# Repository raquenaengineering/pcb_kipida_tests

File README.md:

# pcb_kipida_tests
PCB to test and validate kipida simulator functionality.

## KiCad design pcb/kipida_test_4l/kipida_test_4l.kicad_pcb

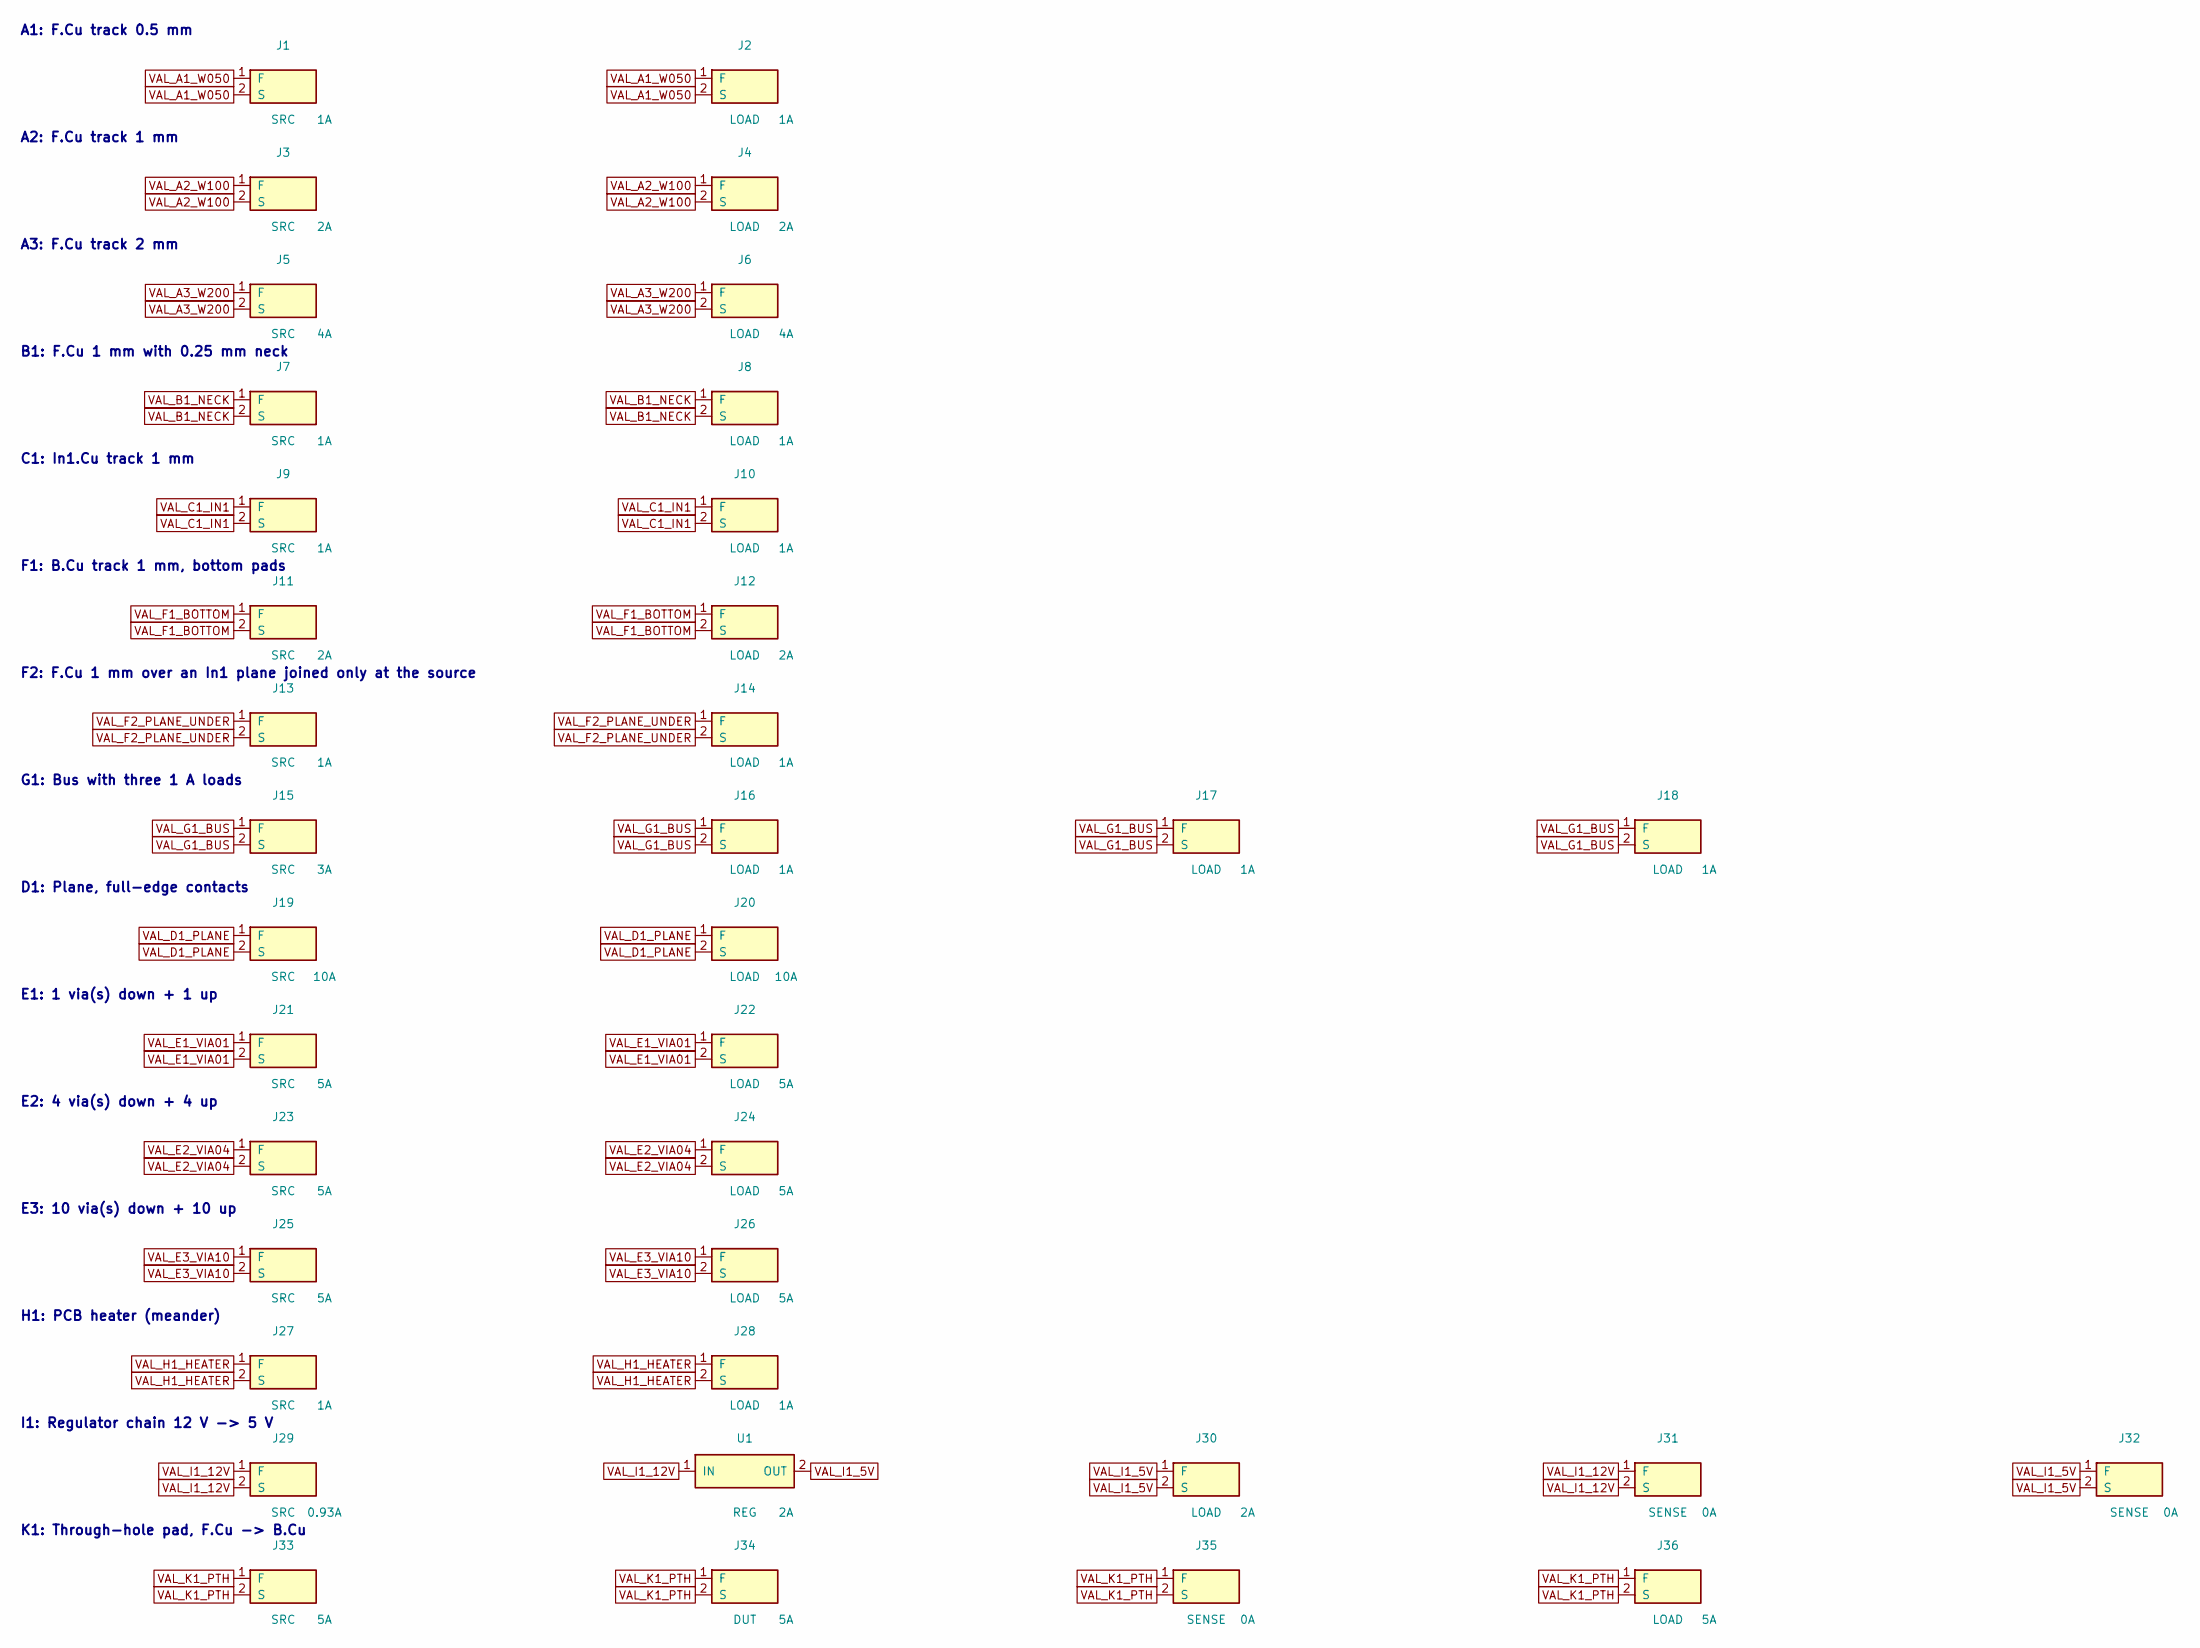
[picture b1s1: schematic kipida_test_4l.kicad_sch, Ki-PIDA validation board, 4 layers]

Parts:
J1: SRC; Terminal_A1_src
J2: LOAD; Terminal_A1_load
J3: SRC; Terminal_A2_src
J4: LOAD; Terminal_A2_load
J5: SRC; Terminal_A3_src
J6: LOAD; Terminal_A3_load
J7: SRC; Terminal_B1_src
J8: LOAD; Terminal_B1_load
J9: SRC; Terminal_C1_src
J10: LOAD; Terminal_C1_load
J11: SRC; Terminal_F1_src
J12: LOAD; Terminal_F1_load
J13: SRC; Terminal_F2_src
J14: LOAD; Terminal_F2_load
J15: SRC; Terminal_G1_src
J16: LOAD; Terminal_G1L1_load
J17: LOAD; Terminal_G1L2_load
J18: LOAD; Terminal_G1L3_load
J19: SRC; Terminal_D1_src
J20: LOAD; Terminal_D1_load
J21: SRC; Terminal_E1_src
J22: LOAD; Terminal_E1_load
J23: SRC; Terminal_E2_src
J24: LOAD; Terminal_E2_load
J25: SRC; Terminal_E3_src
J26: LOAD; Terminal_E3_load
J27: SRC; Terminal_H1_src
J28: LOAD; Terminal_H1_load
J29: SRC; Terminal_I1_src
J30: LOAD; Terminal_I1_load
J31, J32: SENSE; Terminal_I1_sense
J33: SRC; Terminal_K1_src
J34: DUT; Terminal_K1_dut
J35: SENSE; Terminal_K1_sense
J36: LOAD; Terminal_K1_load
U1: REG; Regulator_I1

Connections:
VAL_A1_W050: J1.1 (F), J1.2 (S), J2.1 (F), J2.2 (S)
VAL_A2_W100: J3.1 (F), J3.2 (S), J4.1 (F), J4.2 (S)
VAL_A3_W200: J5.1 (F), J5.2 (S), J6.1 (F), J6.2 (S)
VAL_B1_NECK: J7.1 (F), J7.2 (S), J8.1 (F), J8.2 (S)
VAL_C1_IN1: J9.1 (F), J9.2 (S), J10.1 (F), J10.2 (S)
VAL_D1_PLANE: J19.1 (F), J19.2 (S), J20.1 (F), J20.2 (S)
VAL_E1_VIA01: J21.1 (F), J21.2 (S), J22.1 (F), J22.2 (S)
VAL_E2_VIA04: J23.1 (F), J23.2 (S), J24.1 (F), J24.2 (S)
VAL_E3_VIA10: J25.1 (F), J25.2 (S), J26.1 (F), J26.2 (S)
VAL_F1_BOTTOM: J11.1 (F), J11.2 (S), J12.1 (F), J12.2 (S)
VAL_F2_PLANE_UNDER: J13.1 (F), J13.2 (S), J14.1 (F), J14.2 (S)
VAL_G1_BUS: J15.1 (F), J15.2 (S), J16.1 (F), J16.2 (S), J17.1 (F), J17.2 (S), J18.1 (F), J18.2 (S)
VAL_H1_HEATER: J27.1 (F), J27.2 (S), J28.1 (F), J28.2 (S)
VAL_I1_5V: J30.1 (F), J30.2 (S), J32.1 (F), J32.2 (S), U1.2 (OUT)
VAL_I1_12V: J29.1 (F), J29.2 (S), J31.1 (F), J31.2 (S), U1.1 (IN)
VAL_K1_PTH: J33.1 (F), J33.2 (S), J34.1 (F), J34.2 (S), J35.1 (F), J35.2 (S), J36.1 (F), J36.2 (S)

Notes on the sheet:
A1: F.Cu track 0.5 mm
A2: F.Cu track 1 mm
A3: F.Cu track 2 mm
B1: F.Cu 1 mm with 0.25 mm neck
C1: In1.Cu track 1 mm
F1: B.Cu track 1 mm, bottom pads
F2: F.Cu 1 mm over an In1 plane joined only at the source
G1: Bus with three 1 A loads
D1: Plane, full-edge contacts
E1: 1 via(s) down + 1 up
E2: 4 via(s) down + 4 up
E3: 10 via(s) down + 10 up
H1: PCB heater (meander)
I1: Regulator chain 12 V -> 5 V
K1: Through-hole pad, F.Cu -> B.Cu

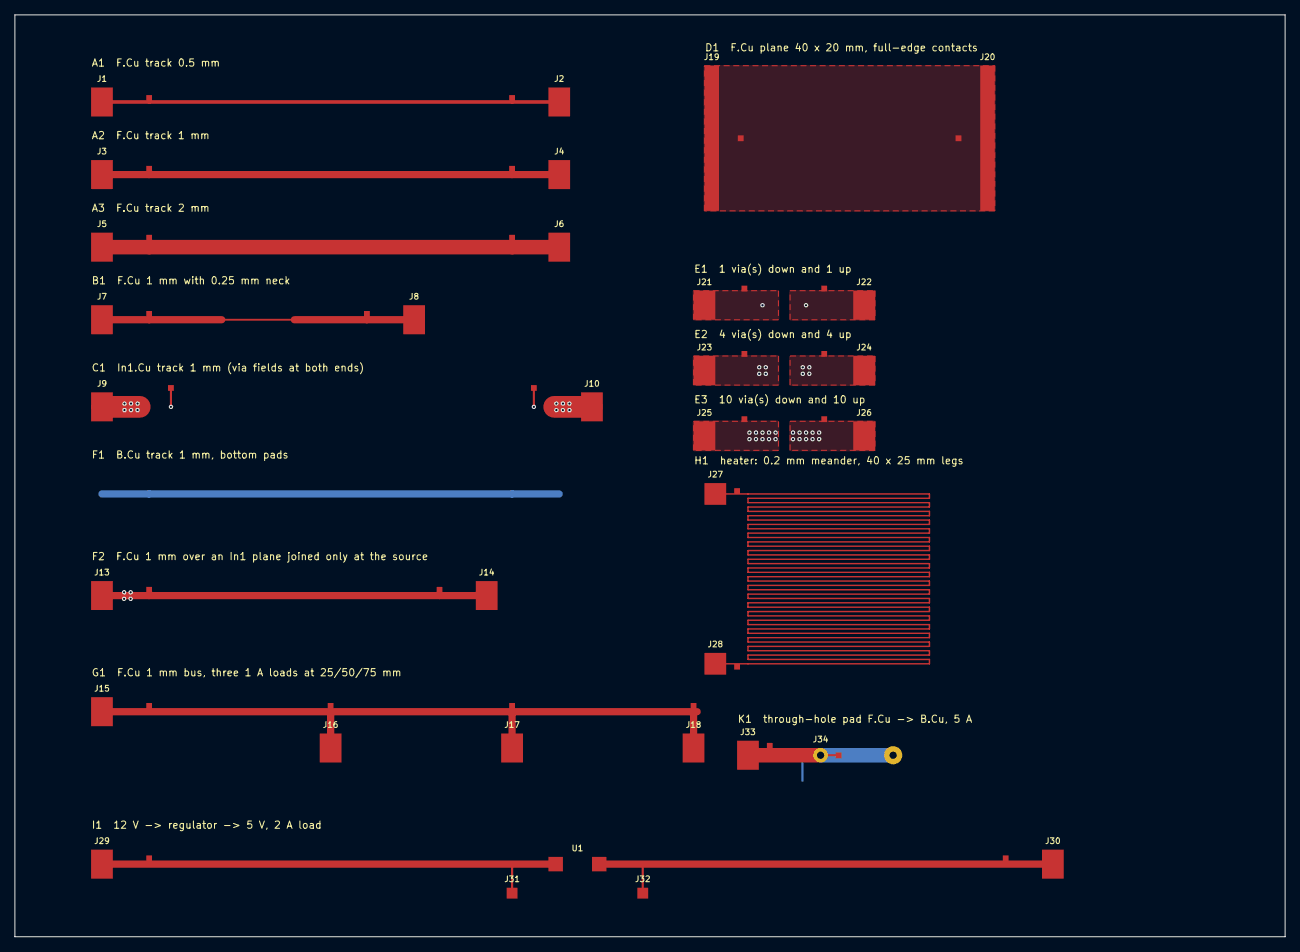
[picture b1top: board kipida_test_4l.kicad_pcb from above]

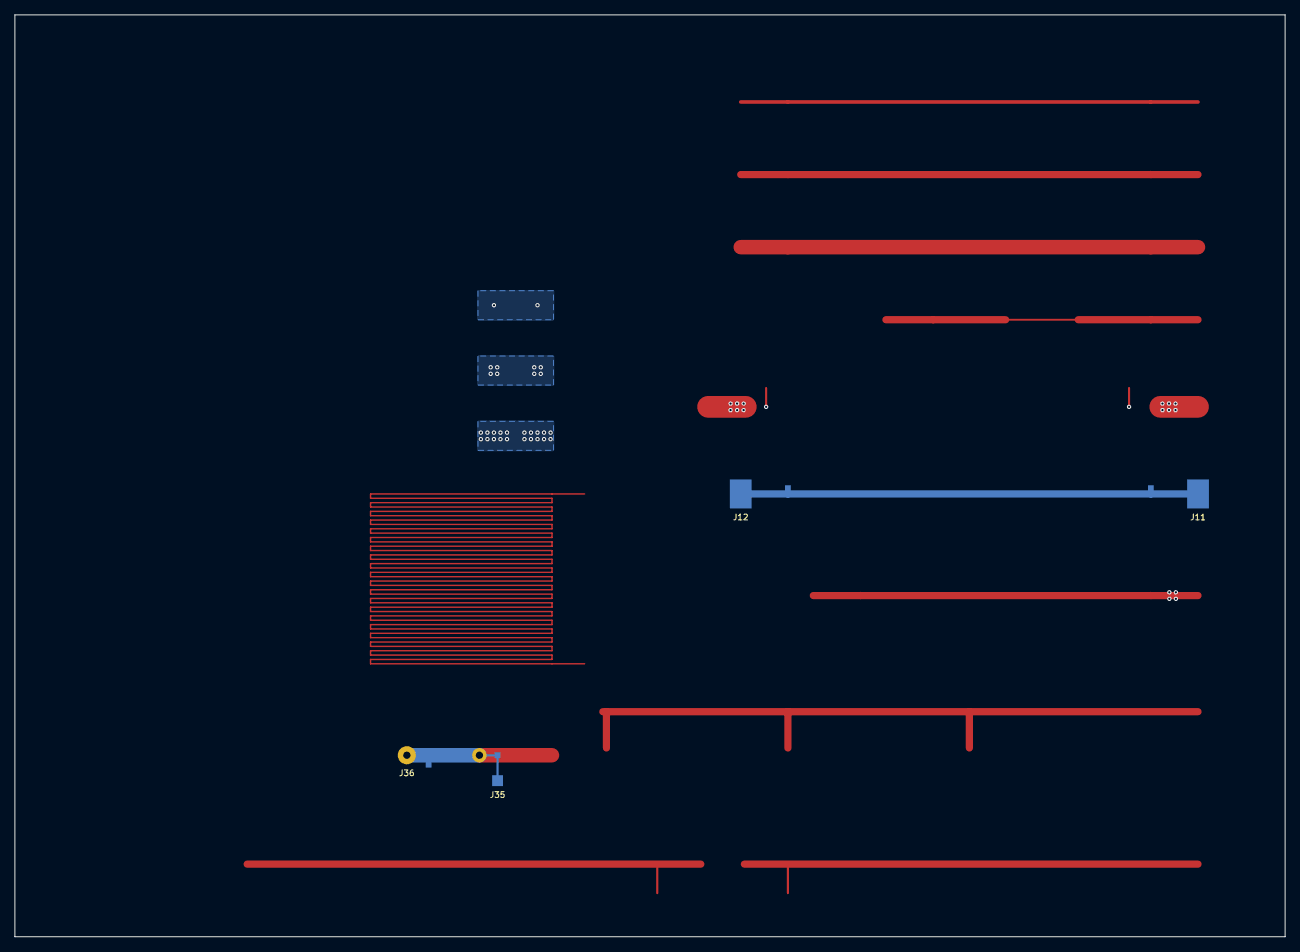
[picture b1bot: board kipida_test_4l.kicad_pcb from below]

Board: 4 copper layers, 175.0 x 127.0 mm, 37 parts (4 on the bottom side), 16 nets.
